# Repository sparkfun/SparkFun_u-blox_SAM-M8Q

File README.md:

SparkFun u-Blox SAM-M8Q
========================================

[*SparkFun u-Blox SAM-M8Q (GPS-15210)*](https://www.sparkfun.com/products/15210)

The SAM-M8Q is a high quality GPS with equally impressive configurability.  We broke out the basic pins and added all the supporting circuitry to make this module even easier to use.  Additionally we've mounted the M8Q on a large ground plane to maximize reception quality.

Repository Contents
-------------------

* **/Documentation** - Data sheets, additional product information
* **/Hardware** - Eagle design files (.brd, .sch)
* **/Production** - Production panel files (.brd)

Documentation
--------------
* **[Installing an Arduino Library Guide](https://learn.sparkfun.com/tutorials/installing-an-arduino-library)** - Basic information on how to install an Arduino library.
* **[Library](https://github.com/sparkfun/SparkFun_u-blox_GNSS_Arduino_Library)** - Arduino Library used with the SparkFun SAM-M8Q 
* **[Hookup Guide](https://learn.sparkfun.com/tutorials/sparkfun-gps-breakout-zoe-m8q-and-sam-m8q-hookup-guide)** - Basic hookup guide for the SparkFun SAM-M8Q.

License Information
-------------------

This product is _**open source**_! 

Please review the LICENSE.md file for license information. 

If you have any questions or concerns on licensing, please contact technical support on our [SparkFun forums](https://forum.sparkfun.com/viewforum.php?f=152).

Distributed as-is; no warranty is given.

- Your friends at SparkFun.

_<COLLABORATION CREDIT>_

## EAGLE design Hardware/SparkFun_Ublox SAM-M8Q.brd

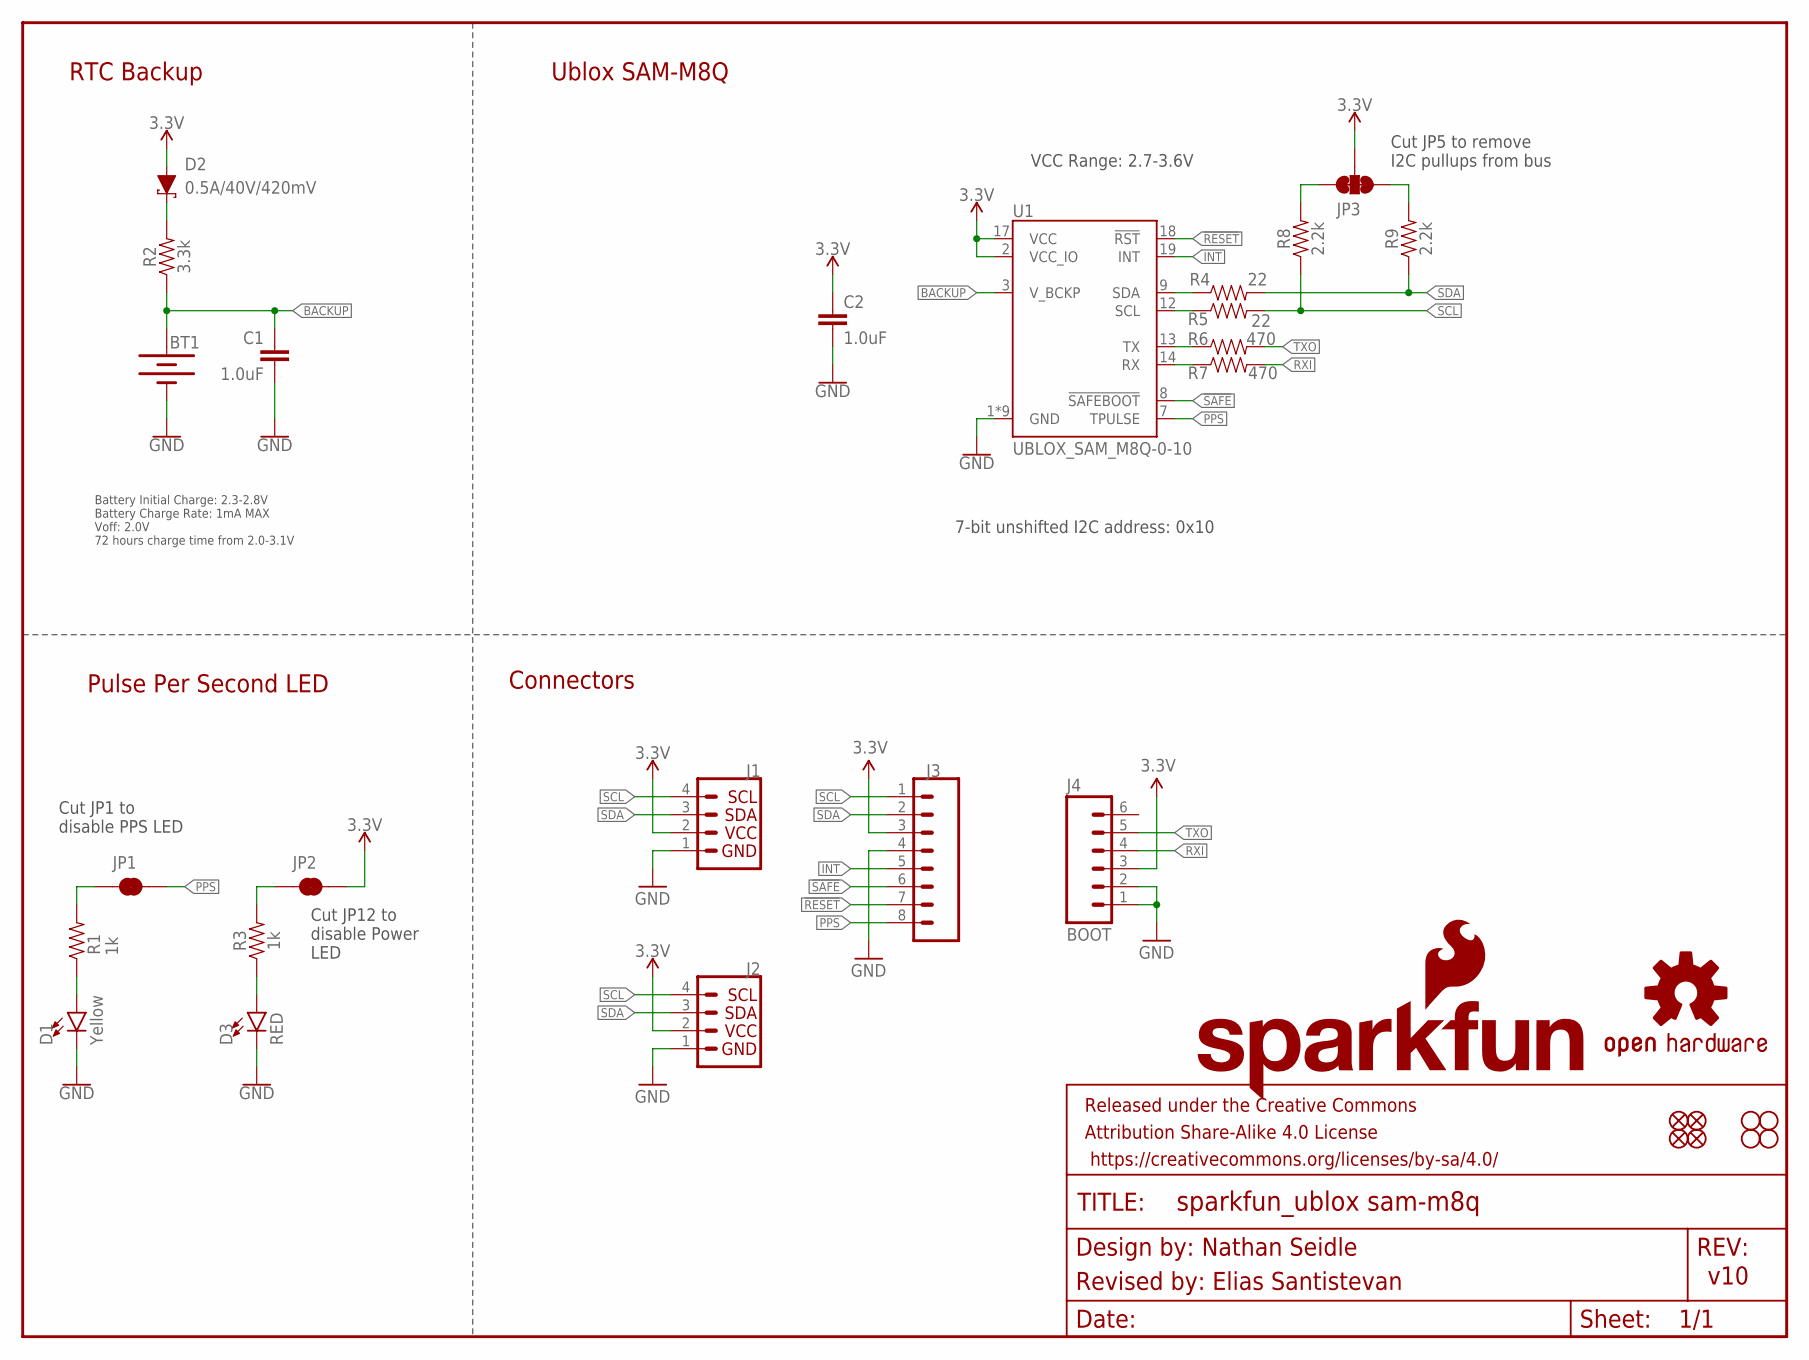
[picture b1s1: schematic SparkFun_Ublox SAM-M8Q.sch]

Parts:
BT1: 6.8MM_COIN_CELL; ML414H_IV01E
C1, C2: 1.0uF; 0603
D1: Yellow; LED-0603
D2: 0.5A/40V/420mV; SOD-323
D3: RED; LED-0603
FD1, FD2, FD3, FD4: FIDUCIALUFIDUCIAL; FIDUCIAL-MICRO
FRAME1: FRAME-LETTER; CREATIVE_COMMONS
H1, H2, H3, H4: STAND-OFF
J1, J2: Qwiic Right Angle; JST04_1MM_RA
J3: CONN_08NO_SILK_FEMALE_PTH; 1X08_NO_SILK
J4: BOOT; 1X06_NO_SILK
JP1, JP2: JUMPER-SMT_2_NC_TRACE_SILK; SMT-JUMPER_2_NC_TRACE_SILK
JP3: JUMPER-SMT_3_2-NC_TRACE_SILK; SMT-JUMPER_3_2-NC_TRACE_SILK
LOGO1: SFE_LOGO_NAME_FLAME.2_INCH; SFE_LOGO_NAME_FLAME_.2
LOGO2: OSHW-LOGOM; OSHW-LOGO-M
R1, R3: 1k; 0603
R2: 3.3k; 0603
R4, R5: 22; 0603
R6, R7: 470; 0603
R8, R9: 2.2k; 0603
U1: UBLOX_SAM_M8Q-0-10; SAM-M8Q

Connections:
3.3V: C2.1, D2.A, J1.2, J2.2, J3.3, J4.3, JP2.2, JP3.2, U1.2 (VCC_IO), U1.17 (VCC)
!RESET: J3.7, U1.18 (!RST)
!SAFE: J3.6, U1.8 (!SAFEBOOT)
BACKUP: BT1.+, C1.1, R2.1, U1.3 (V_BCKP)
GND: BT1.-, C1.2, C2.2, D1.C, D3.C, J1.1, J2.1, J3.4, J4.1, J4.2, U1.1 (GND), U1.4 (GND), U1.5 (GND), U1.6 (GND), U1.10 (GND), U1.11 (GND), U1.15 (GND), U1.16 (GND), U1.20 (GND)
INT: J3.5, U1.19 (INT)
unnamed: JP2.1, R3.2
unnamed: D1.A, R1.1
unnamed: D3.A, R3.1
unnamed: JP1.1, R1.2
unnamed: JP3.1, R9.2
unnamed: D2.C, R2.2
unnamed: JP3.3, R8.2
PPS: J3.8, JP1.2, U1.7 (TPULSE)
RXI: J4.4, R7.2
RXLV: R7.1, U1.14 (RX)
SCL: J1.4, J2.4, J3.1, R5.2, R8.1
SCL_LV: R5.1, U1.12 (SCL)
SDA: J1.3, J2.3, J3.2, R4.2, R9.1
SDA_LV: R4.1, U1.9 (SDA)
TXLV: R6.1, U1.13 (TX)
TXO: J4.5, R6.2

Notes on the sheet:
v10
7-bit unshifted I2C address: 0x10
Ublox SAM-M8Q
RTC Backup
Pulse Per Second LED
Cut JP5 to remove I2C pullups from bus
Cut JP1 to disable PPS LED
Revised by: Elias Santistevan
Nathan Seidle
Connectors
Cut JP12 to disable Power LED
VCC Range: 2.7-3.6V
Battery Initial Charge: 2.3-2.8V Battery Charge Rate: 1mA MAX Voff: 2.0V 72 hours charge time from 2.0-3.1V

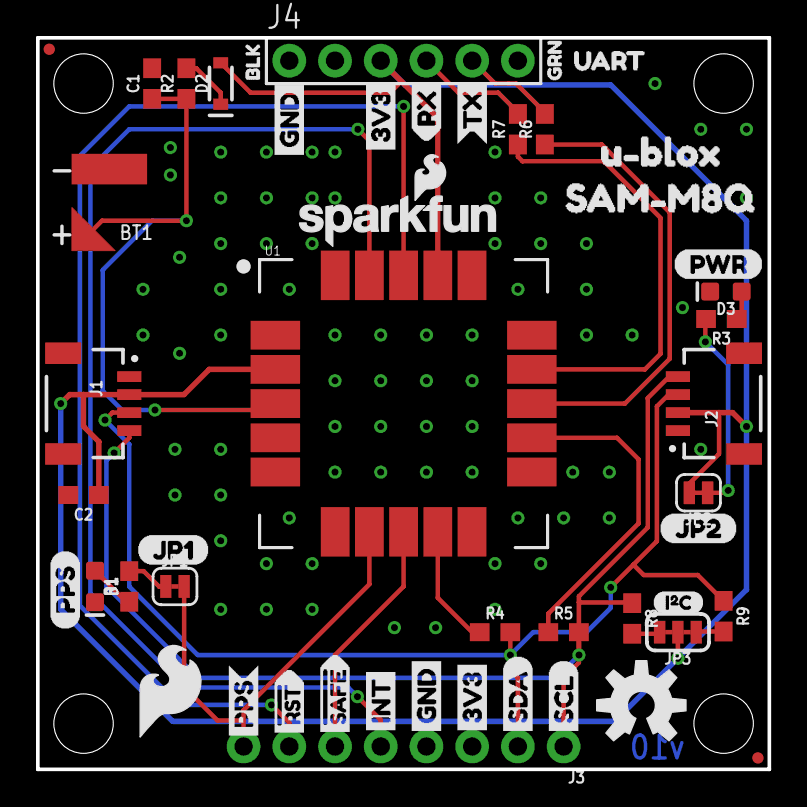
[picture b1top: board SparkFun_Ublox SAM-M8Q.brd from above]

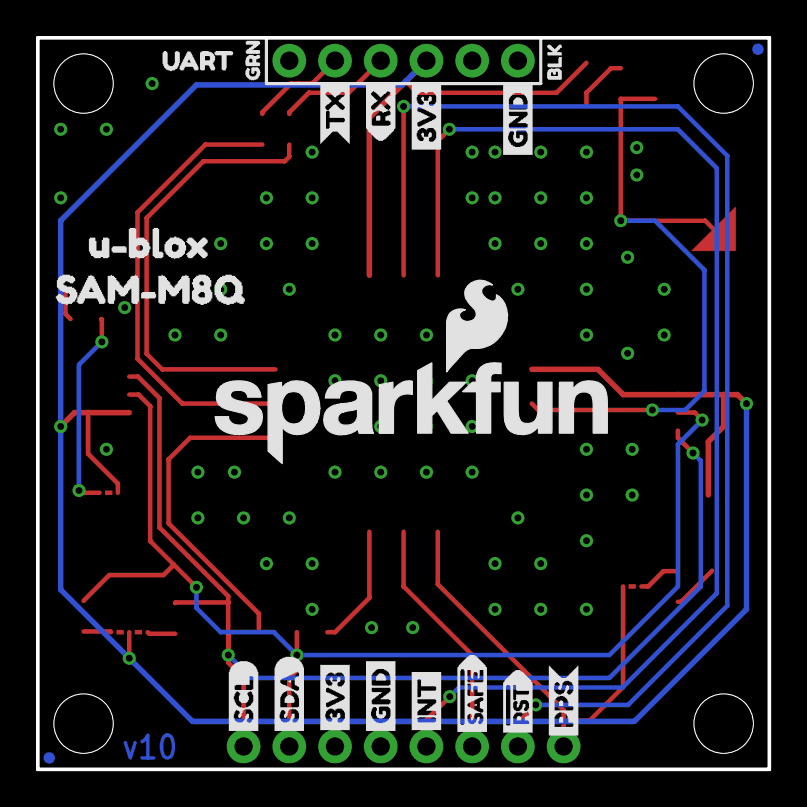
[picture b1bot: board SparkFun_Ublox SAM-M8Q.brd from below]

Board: 2 copper layers, 40.6 x 40.6 mm, 75 parts (20 on the bottom side), 22 nets.

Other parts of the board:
U$1, U$4: SDA-[)
U$2: SFE_LOGO_FLAME_.2
U$3, U$5: SCL-[)
U$6, U$7, U$27, U$32: 3V3-04
U$8, U$9, U$33, U$34: GND-04
U$10: I_SUPER2_C-()-03
U$11, U$45: UART0
U$12, U$13: BLK1
U$14, U$17: GRN2
U$15, U$16: INT8
U$18: JP10
U$19, U$20: RX6
U$21, U$25: SAM#M8Q4
U$22, U$26: U#BLOX3
U$23, U$24: TX7
U$28: SFE_LOGO_NAME_FLAME_.1
U$29: PPS0
U$30: PWR0
U$31: JP20
U$35, U$36: #RST3
U$39, U$40: #SAFE1
U$43, U$44: PPS5

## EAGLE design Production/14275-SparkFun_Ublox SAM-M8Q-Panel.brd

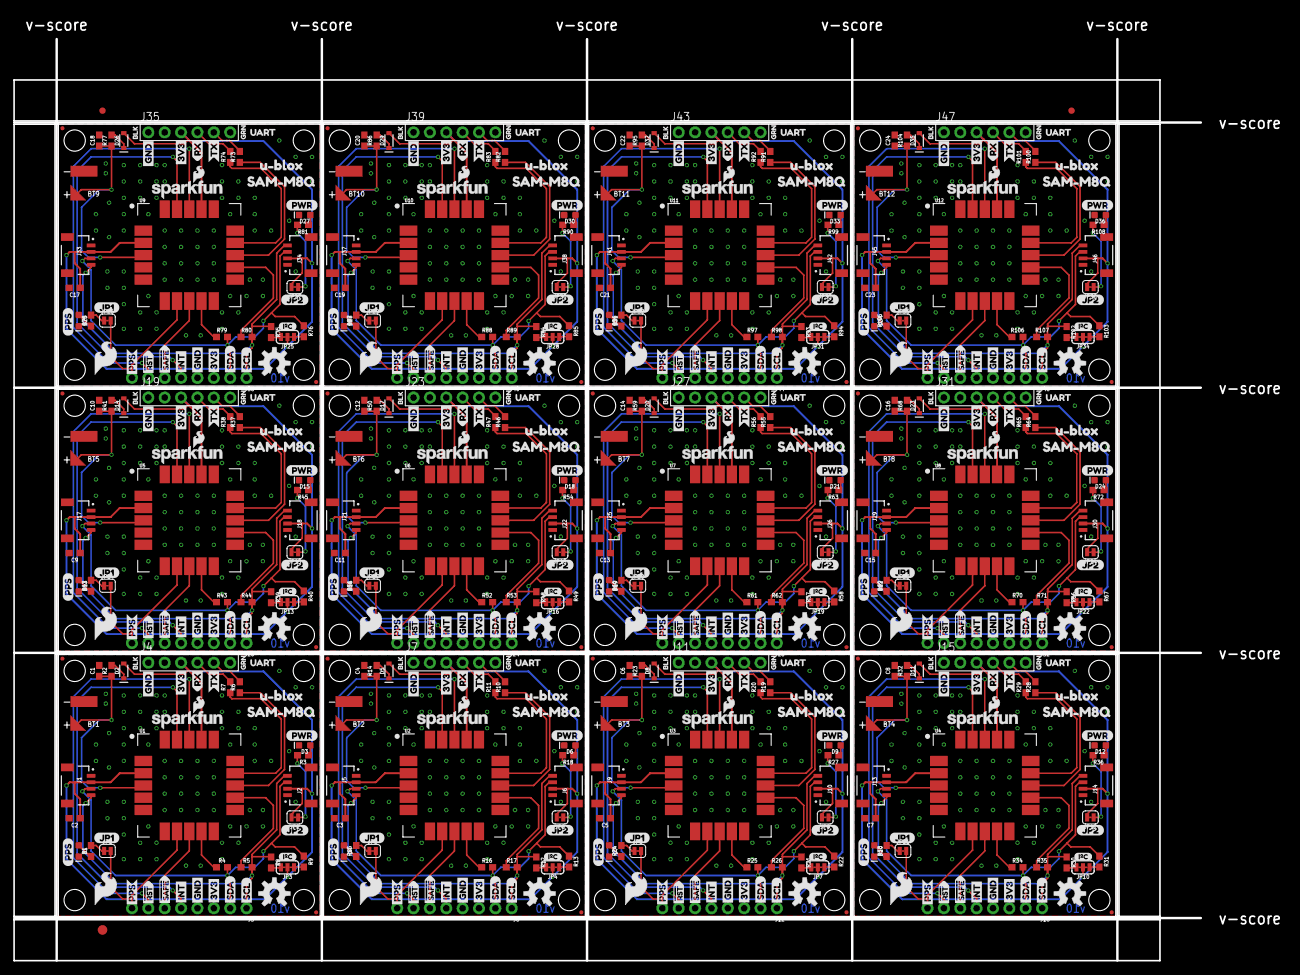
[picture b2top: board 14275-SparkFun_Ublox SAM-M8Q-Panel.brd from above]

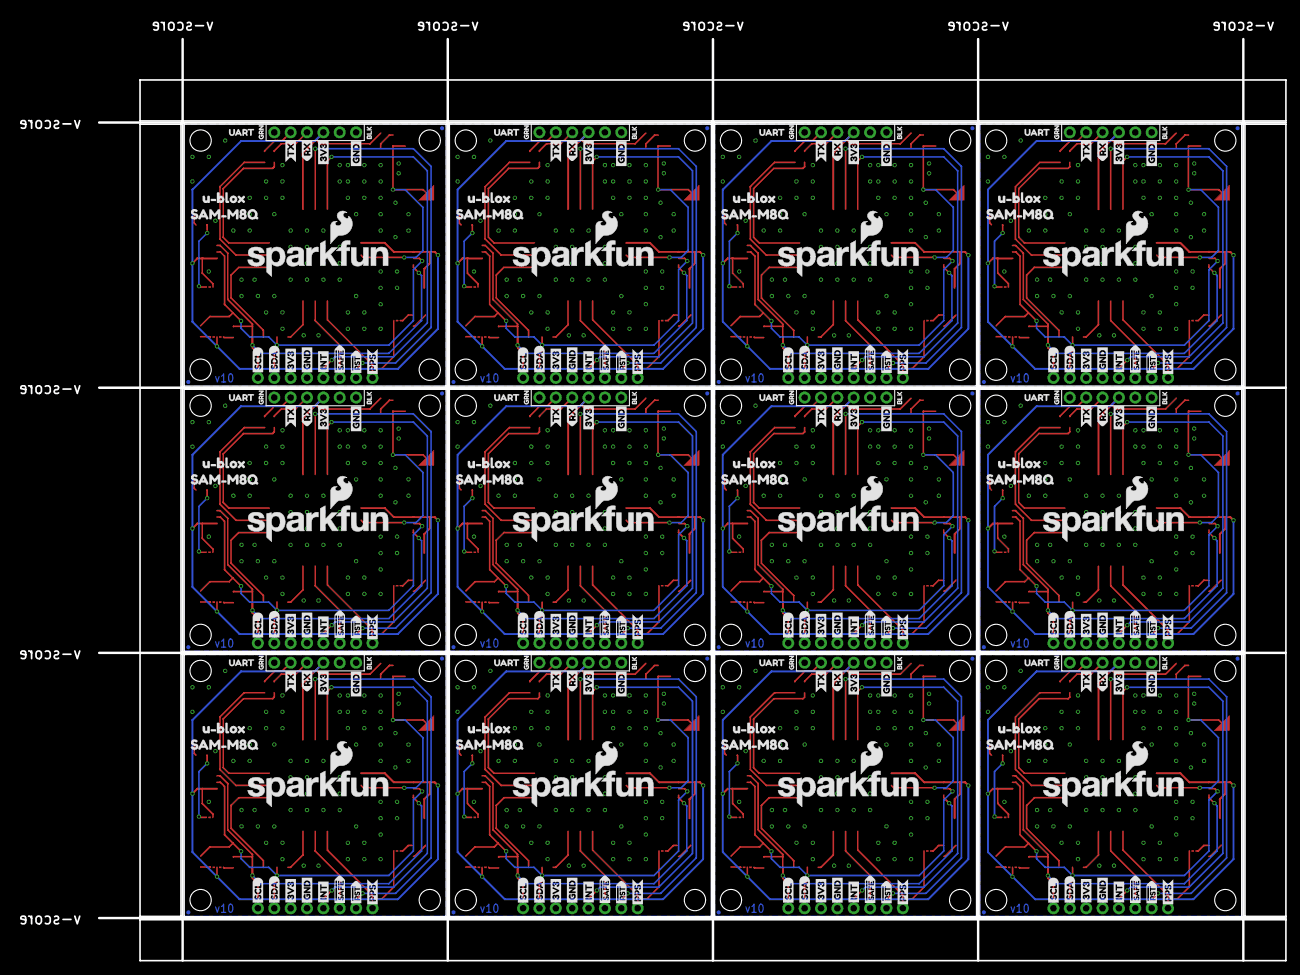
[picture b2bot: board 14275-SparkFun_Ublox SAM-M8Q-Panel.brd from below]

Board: 2 copper layers, 184.2 x 143.0 mm, 891 parts (240 on the bottom side), 264 nets.

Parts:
BT1, BT2, BT3, BT4, BT5, BT6, BT7, BT8, BT9, BT10, BT11, BT12: 6.8MM_COIN_CELL; ML414H_IV01E
C1, C2, C3, C4, C5, C6, C7, C8, C9, C10, C11, C12, C13, C14, C15, C16, C17, C18, C19, C20, C21, C22, C23, C24: 1.0uF; 0603
D1, D4, D7, D10, D13, D16, D19, D22, D25, D28, D31, D34: Yellow; LED-0603
D2, D5, D8, D11, D14, D17, D20, D23, D26, D29, D32, D35: 0.5A/40V/420mV; SOD-323
D3, D6, D9, D12, D15, D18, D21, D24, D27, D30, D33, D36: RED; LED-0603
E$1, E$2: FIDUCIAL-1X2
E$3: FIDUCIAL-1.5X3
FD1, FD2, FD3, FD4, FD5, FD6, FD7, FD8, FD9, FD10, FD11, FD12, FD13, FD14, FD15, FD16, FD17, FD18, FD19, FD20, FD21, FD22, FD23, FD24, FD25, FD26, FD27, FD28, FD29, FD30, FD31, FD32, FD33, FD34, FD35, FD36, FD37, FD38, FD39, FD40, FD41, FD42, FD43, FD44, FD45, FD46, FD47, FD48: FIDUCIALUFIDUCIAL; FIDUCIAL-MICRO
H1, H2, H3, H4, H5, H6, H7, H8, H9, H10, H11, H12, H13, H14, H15, H16, H17, H18, H19, H20, H21, H22, H23, H24, H25, H26, H27, H28, H29, H30, H31, H32, H33, H34, H35, H36, H37, H38, H39, H40, H41, H42, H43, H44, H45, H46, H47, H48: STAND-OFF
J1, J2, J5, J6, J9, J10, J13, J14, J17, J18, J21, J22, J25, J26, J29, J30, J33, J34, J37, J38, J41, J42, J45, J46: Qwiic Right Angle; JST04_1MM_RA
J3, J8, J12, J16, J20, J24, J28, J32, J36, J40, J44, J48: 1X08_NO_SILK
J4, J7, J11, J15, J19, J23, J27, J31, J35, J39, J43, J47: BOOT; 1X06_NO_SILK
JP1, JP5, JP8, JP11, JP14, JP17, JP20, JP23, JP26, JP29, JP32, JP35: SMT-JUMPER_2_NC_TRACE_SILK
JP2, JP6, JP9, JP12, JP15, JP18, JP21, JP24, JP27, JP30, JP33, JP36: JUMPER-SMT_2_NC_TRACE_SILK; SMT-JUMPER_2_NC_TRACE_SILK
JP3, JP4, JP7, JP10, JP13, JP16, JP19, JP22, JP25, JP28, JP31, JP34: JUMPER-SMT_3_2-NC_TRACE_SILK; SMT-JUMPER_3_2-NC_TRACE_SILK
LOGO1, LOGO4, LOGO6, LOGO8, LOGO10, LOGO12, LOGO14, LOGO16, LOGO18, LOGO20, LOGO22, LOGO24: SFE_LOGO_NAME_FLAME.2_INCH; SFE_LOGO_NAME_FLAME_.2
LOGO2, LOGO3, LOGO5, LOGO7, LOGO9, LOGO11, LOGO13, LOGO15, LOGO17, LOGO19, LOGO21, LOGO23: OSHW-LOGOM; OSHW-LOGO-M
R1, R3, R15, R18, R24, R27, R33, R36, R42, R45, R51, R54, R60, R63, R69, R72, R78, R81, R87, R90, R96, R99, R105, R108: 1k; 0603
R2, R14, R23, R32, R41, R50, R59, R68, R77, R86, R95, R104: 3.3k; 0603
R4, R5, R16, R17, R25, R26, R34, R35, R43, R44, R52, R53, R61, R62, R70, R71, R79, R80, R88, R89, R97, R98, R106, R107: 22; 0603
R6, R7, R10, R11, R19, R20, R28, R29, R37, R38, R46, R47, R55, R56, R64, R65, R73, R74, R82, R83, R91, R92, R100, R101: 470; 0603
R8, R9, R12, R13, R21, R22, R30, R31, R39, R40, R48, R49, R57, R58, R66, R67, R75, R76, R84, R85, R93, R94, R102, R103: 2.2k; 0603
U1, U2, U3, U4, U5, U6, U7, U8, U9, U10, U11, U12: UBLOX_SAM_M8Q-0-10; SAM-M8Q
U$1, U$4, U$37, U$41, U$83, U$85, U$124, U$126, U$165, U$167, U$206, U$208, U$247, U$249, U$288, U$290, U$329, U$331, U$370, U$372, U$411, U$413, U$452, U$454: SDA-[)
U$2, U$80, U$121, U$162, U$203, U$244, U$285, U$326, U$367, U$408, U$449, U$490: SFE_LOGO_FLAME_.2
U$3, U$5, U$38, U$42, U$84, U$86, U$125, U$127, U$166, U$168, U$207, U$209, U$248, U$250, U$289, U$291, U$330, U$332, U$371, U$373, U$412, U$414, U$453, U$455: SCL-[)
U$6, U$7, U$27, U$32, U$46, U$47, U$62, U$63, U$87, U$88, U$103, U$104, U$128, U$129, U$144, U$145, U$169, U$170, U$185, U$186, U$210, U$211, U$226, U$227, U$251, U$252, U$267, U$268, U$292, U$293, U$308, U$309, U$333, U$334, U$349, U$350, U$374, U$375, U$390, U$391, U$415, U$416, U$431, U$432, U$456, U$457, U$472, U$473: 3V3-04
U$8, U$9, U$33, U$34, U$48, U$49, U$64, U$65, U$89, U$90, U$105, U$106, U$130, U$131, U$146, U$147, U$171, U$172, U$187, U$188, U$212, U$213, U$228, U$229, U$253, U$254, U$269, U$270, U$294, U$295, U$310, U$311, U$335, U$336, U$351, U$352, U$376, U$377, U$392, U$393, U$417, U$418, U$433, U$434, U$458, U$459, U$474, U$475: GND-04
U$10, U$50, U$91, U$132, U$173, U$214, U$255, U$296, U$337, U$378, U$419, U$460: I_SUPER2_C-()-03
U$11, U$45, U$72, U$73, U$113, U$114, U$154, U$155, U$195, U$196, U$236, U$237, U$277, U$278, U$318, U$319, U$359, U$360, U$400, U$401, U$441, U$442, U$482, U$483: UART0
U$12, U$13, U$74, U$75, U$115, U$116, U$156, U$157, U$197, U$198, U$238, U$239, U$279, U$280, U$320, U$321, U$361, U$362, U$402, U$403, U$443, U$444, U$484, U$485: BLK1
U$14, U$17, U$76, U$77, U$117, U$118, U$158, U$159, U$199, U$200, U$240, U$241, U$281, U$282, U$322, U$323, U$363, U$364, U$404, U$405, U$445, U$446, U$486, U$487: GRN2
U$15, U$16, U$51, U$52, U$92, U$93, U$133, U$134, U$174, U$175, U$215, U$216, U$256, U$257, U$297, U$298, U$338, U$339, U$379, U$380, U$420, U$421, U$461, U$462: INT8
U$18, U$78, U$119, U$160, U$201, U$242, U$283, U$324, U$365, U$406, U$447, U$488: JP10
U$19, U$20, U$53, U$54, U$94, U$95, U$135, U$136, U$176, U$177, U$217, U$218, U$258, U$259, U$299, U$300, U$340, U$341, U$381, U$382, U$422, U$423, U$463, U$464: RX6
U$21, U$25, U$55, U$60, U$96, U$101, U$137, U$142, U$178, U$183, U$219, U$224, U$260, U$265, U$301, U$306, U$342, U$347, U$383, U$388, U$424, U$429, U$465, U$470: SAM#M8Q4
U$22, U$26, U$58, U$59, U$99, U$100, U$140, U$141, U$181, U$182, U$222, U$223, U$263, U$264, U$304, U$305, U$345, U$346, U$386, U$387, U$427, U$428, U$468, U$469: U#BLOX3
U$23, U$24, U$56, U$57, U$97, U$98, U$138, U$139, U$179, U$180, U$220, U$221, U$261, U$262, U$302, U$303, U$343, U$344, U$384, U$385, U$425, U$426, U$466, U$467: TX7
U$28, U$82, U$123, U$164, U$205, U$246, U$287, U$328, U$369, U$410, U$451, U$492: SFE_LOGO_NAME_FLAME_.1
U$29, U$61, U$102, U$143, U$184, U$225, U$266, U$307, U$348, U$389, U$430, U$471: PPS0
U$30, U$79, U$120, U$161, U$202, U$243, U$284, U$325, U$366, U$407, U$448, U$489: PWR0
U$31, U$81, U$122, U$163, U$204, U$245, U$286, U$327, U$368, U$409, U$450, U$491: JP20
U$35, U$36, U$66, U$67, U$107, U$108, U$148, U$149, U$189, U$190, U$230, U$231, U$271, U$272, U$312, U$313, U$353, U$354, U$394, U$395, U$435, U$436, U$476, U$477: #RST3
U$39, U$40, U$68, U$69, U$109, U$110, U$150, U$151, U$191, U$192, U$232, U$233, U$273, U$274, U$314, U$315, U$355, U$356, U$396, U$397, U$437, U$438, U$478, U$479: #SAFE1
U$43, U$44, U$70, U$71, U$111, U$112, U$152, U$153, U$193, U$194, U$234, U$235, U$275, U$276, U$316, U$317, U$357, U$358, U$398, U$399, U$439, U$440, U$480, U$481: PPS5

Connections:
3.3V: C2.1, D2.A, J1.2, J2.2, J3.3, J4.3, JP2.2, JP3.2, U1.2, U1.17
3.3V1: C3.1, D5.A, J5.2, J6.2, J7.3, J8.3, JP4.2, JP6.2, U2.2, U2.17
3.3V2: C5.1, D8.A, J9.2, J10.2, J11.3, J12.3, JP7.2, JP9.2, U3.2, U3.17
3.3V3: C7.1, D11.A, J13.2, J14.2, J15.3, J16.3, JP10.2, JP12.2, U4.2, U4.17
3.3V4: C9.1, D14.A, J17.2, J18.2, J19.3, J20.3, JP13.2, JP15.2, U5.2, U5.17
3.3V5: C11.1, D17.A, J21.2, J22.2, J23.3, J24.3, JP16.2, JP18.2, U6.2, U6.17
3.3V6: C13.1, D20.A, J25.2, J26.2, J27.3, J28.3, JP19.2, JP21.2, U7.2, U7.17
3.3V7: C15.1, D23.A, J29.2, J30.2, J31.3, J32.3, JP22.2, JP24.2, U8.2, U8.17
3.3V8: C17.1, D26.A, J33.2, J34.2, J35.3, J36.3, JP25.2, JP27.2, U9.2, U9.17
3.3V9: C19.1, D29.A, J37.2, J38.2, J39.3, J40.3, JP28.2, JP30.2, U10.2, U10.17
3.3V10: C21.1, D32.A, J41.2, J42.2, J43.3, J44.3, JP31.2, JP33.2, U11.2, U11.17
3.3V11: C23.1, D35.A, J45.2, J46.2, J47.3, J48.3, JP34.2, JP36.2, U12.2, U12.17
!RESET: J3.7, U1.18
!RESET1: J8.7, U2.18
!RESET2: J12.7, U3.18
!RESET3: J16.7, U4.18
!RESET4: J20.7, U5.18
!RESET5: J24.7, U6.18
!RESET6: J28.7, U7.18
!RESET7: J32.7, U8.18
!RESET8: J36.7, U9.18
!RESET9: J40.7, U10.18
!RESET10: J44.7, U11.18
!RESET11: J48.7, U12.18
!SAFE: J3.6, U1.8
!SAFE1: J8.6, U2.8
!SAFE2: J12.6, U3.8
!SAFE3: J16.6, U4.8
!SAFE4: J20.6, U5.8
!SAFE5: J24.6, U6.8
!SAFE6: J28.6, U7.8
!SAFE7: J32.6, U8.8
!SAFE8: J36.6, U9.8
!SAFE9: J40.6, U10.8
!SAFE10: J44.6, U11.8
!SAFE11: J48.6, U12.8
BACKUP: BT1.+, C1.1, R2.1, U1.3
BACKUP1: BT2.+, C4.1, R14.1, U2.3
BACKUP2: BT3.+, C6.1, R23.1, U3.3
BACKUP3: BT4.+, C8.1, R32.1, U4.3
BACKUP4: BT5.+, C10.1, R41.1, U5.3
BACKUP5: BT6.+, C12.1, R50.1, U6.3
BACKUP6: BT7.+, C14.1, R59.1, U7.3
BACKUP7: BT8.+, C16.1, R68.1, U8.3
BACKUP8: BT9.+, C18.1, R77.1, U9.3
BACKUP9: BT10.+, C20.1, R86.1, U10.3
BACKUP10: BT11.+, C22.1, R95.1, U11.3
BACKUP11: BT12.+, C24.1, R104.1, U12.3
GND: BT1.-, C1.2, C2.2, D1.C, D3.C, J1.1, J2.1, J3.4, J4.1, J4.2, U1.1, U1.4, U1.5, U1.6, U1.10, U1.11, U1.15, U1.16, U1.20
GND1: BT2.-, C3.2, C4.2, D4.C, D6.C, J5.1, J6.1, J7.1, J7.2, J8.4, U2.1, U2.4, U2.5, U2.6, U2.10, U2.11, U2.15, U2.16, U2.20
GND2: BT3.-, C5.2, C6.2, D7.C, D9.C, J9.1, J10.1, J11.1, J11.2, J12.4, U3.1, U3.4, U3.5, U3.6, U3.10, U3.11, U3.15, U3.16, U3.20
GND3: BT4.-, C7.2, C8.2, D10.C, D12.C, J13.1, J14.1, J15.1, J15.2, J16.4, U4.1, U4.4, U4.5, U4.6, U4.10, U4.11, U4.15, U4.16, U4.20
GND4: BT5.-, C9.2, C10.2, D13.C, D15.C, J17.1, J18.1, J19.1, J19.2, J20.4, U5.1, U5.4, U5.5, U5.6, U5.10, U5.11, U5.15, U5.16, U5.20
GND5: BT6.-, C11.2, C12.2, D16.C, D18.C, J21.1, J22.1, J23.1, J23.2, J24.4, U6.1, U6.4, U6.5, U6.6, U6.10, U6.11, U6.15, U6.16, U6.20
GND6: BT7.-, C13.2, C14.2, D19.C, D21.C, J25.1, J26.1, J27.1, J27.2, J28.4, U7.1, U7.4, U7.5, U7.6, U7.10, U7.11, U7.15, U7.16, U7.20
GND7: BT8.-, C15.2, C16.2, D22.C, D24.C, J29.1, J30.1, J31.1, J31.2, J32.4, U8.1, U8.4, U8.5, U8.6, U8.10, U8.11, U8.15, U8.16, U8.20
GND8: BT9.-, C17.2, C18.2, D25.C, D27.C, J33.1, J34.1, J35.1, J35.2, J36.4, U9.1, U9.4, U9.5, U9.6, U9.10, U9.11, U9.15, U9.16, U9.20
GND9: BT10.-, C19.2, C20.2, D28.C, D30.C, J37.1, J38.1, J39.1, J39.2, J40.4, U10.1, U10.4, U10.5, U10.6, U10.10, U10.11, U10.15, U10.16, U10.20
GND10: BT11.-, C21.2, C22.2, D31.C, D33.C, J41.1, J42.1, J43.1, J43.2, J44.4, U11.1, U11.4, U11.5, U11.6, U11.10, U11.11, U11.15, U11.16, U11.20
GND11: BT12.-, C23.2, C24.2, D34.C, D36.C, J45.1, J46.1, J47.1, J47.2, J48.4, U12.1, U12.4, U12.5, U12.6, U12.10, U12.11, U12.15, U12.16, U12.20
INT: J3.5, U1.19
INT1: J8.5, U2.19
INT2: J12.5, U3.19
INT3: J16.5, U4.19
INT4: J20.5, U5.19
INT5: J24.5, U6.19
INT6: J28.5, U7.19
INT7: J32.5, U8.19
INT8: J36.5, U9.19
INT9: J40.5, U10.19
INT10: J44.5, U11.19
INT11: J48.5, U12.19
unnamed: JP2.1, R3.2
unnamed: D1.A, R1.1
unnamed: D3.A, R3.1
unnamed: JP1.1, R1.2
unnamed: JP3.1, R9.2
unnamed: D2.C, R2.2
unnamed: JP4.1, R13.2
unnamed: JP3.3, R8.2
unnamed: JP4.3, R12.2
unnamed: D4.A, R15.1
unnamed: JP5.1, R15.2
unnamed: D5.C, R14.2
unnamed: JP6.1, R18.2
unnamed: D6.A, R18.1
unnamed: JP7.1, R22.2
unnamed: JP7.3, R21.2
unnamed: D7.A, R24.1
unnamed: JP8.1, R24.2
unnamed: D8.C, R23.2
unnamed: JP9.1, R27.2
unnamed: D9.A, R27.1
unnamed: JP10.1, R31.2
unnamed: JP10.3, R30.2
unnamed: D10.A, R33.1
unnamed: JP11.1, R33.2
unnamed: D11.C, R32.2
unnamed: JP12.1, R36.2
unnamed: D12.A, R36.1
unnamed: JP13.1, R40.2
unnamed: JP13.3, R39.2
unnamed: D13.A, R42.1
unnamed: JP14.1, R42.2
unnamed: D14.C, R41.2
unnamed: JP15.1, R45.2
unnamed: D15.A, R45.1
unnamed: JP16.1, R49.2
unnamed: JP16.3, R48.2
unnamed: D16.A, R51.1
unnamed: JP17.1, R51.2
unnamed: D17.C, R50.2
unnamed: JP18.1, R54.2
unnamed: D18.A, R54.1
unnamed: JP19.1, R58.2
unnamed: JP19.3, R57.2
unnamed: D19.A, R60.1
unnamed: JP20.1, R60.2
unnamed: D20.C, R59.2
unnamed: JP21.1, R63.2
unnamed: D21.A, R63.1
unnamed: JP22.1, R67.2
unnamed: JP22.3, R66.2
unnamed: D22.A, R69.1
unnamed: JP23.1, R69.2
unnamed: D23.C, R68.2
unnamed: JP24.1, R72.2
unnamed: D24.A, R72.1
unnamed: JP25.1, R76.2
unnamed: JP25.3, R75.2
unnamed: D25.A, R78.1
unnamed: JP26.1, R78.2
unnamed: D26.C, R77.2
unnamed: JP27.1, R81.2
unnamed: D27.A, R81.1
unnamed: JP28.1, R85.2
unnamed: JP28.3, R84.2
unnamed: D28.A, R87.1
unnamed: JP29.1, R87.2
unnamed: D29.C, R86.2
unnamed: JP30.1, R90.2
unnamed: D30.A, R90.1
unnamed: JP31.1, R94.2
unnamed: JP31.3, R93.2
unnamed: D31.A, R96.1
unnamed: JP32.1, R96.2
unnamed: D32.C, R95.2
unnamed: JP33.1, R99.2
unnamed: D33.A, R99.1
unnamed: JP34.1, R103.2
unnamed: JP34.3, R102.2
unnamed: D34.A, R105.1
unnamed: JP35.1, R105.2
unnamed: D35.C, R104.2
unnamed: JP36.1, R108.2
unnamed: D36.A, R108.1
PPS: J3.8, JP1.2, U1.7
PPS1: J8.8, JP5.2, U2.7
PPS2: J12.8, JP8.2, U3.7
PPS3: J16.8, JP11.2, U4.7
PPS4: J20.8, JP14.2, U5.7
PPS5: J24.8, JP17.2, U6.7
PPS6: J28.8, JP20.2, U7.7
PPS7: J32.8, JP23.2, U8.7
PPS8: J36.8, JP26.2, U9.7
PPS9: J40.8, JP29.2, U10.7
PPS10: J44.8, JP32.2, U11.7
PPS11: J48.8, JP35.2, U12.7
RXI: J4.4, R7.2
RXI1: J7.4, R11.2
RXI2: J11.4, R20.2
RXI3: J15.4, R29.2
RXI4: J19.4, R38.2
RXI5: J23.4, R47.2
RXI6: J27.4, R56.2
RXI7: J31.4, R65.2
RXI8: J35.4, R74.2
RXI9: J39.4, R83.2
RXI10: J43.4, R92.2
RXI11: J47.4, R101.2
RXLV: R7.1, U1.14
RXLV1: R11.1, U2.14
RXLV2: R20.1, U3.14
RXLV3: R29.1, U4.14
RXLV4: R38.1, U5.14
RXLV5: R47.1, U6.14
RXLV6: R56.1, U7.14
RXLV7: R65.1, U8.14
RXLV8: R74.1, U9.14
RXLV9: R83.1, U10.14
RXLV10: R92.1, U11.14
RXLV11: R101.1, U12.14
SCL: J1.4, J2.4, J3.1, R5.2, R8.1
SCL1: J5.4, J6.4, J8.1, R12.1, R17.2
SCL2: J9.4, J10.4, J12.1, R21.1, R26.2
SCL3: J13.4, J14.4, J16.1, R30.1, R35.2
SCL4: J17.4, J18.4, J20.1, R39.1, R44.2
SCL5: J21.4, J22.4, J24.1, R48.1, R53.2
SCL6: J25.4, J26.4, J28.1, R57.1, R62.2
SCL7: J29.4, J30.4, J32.1, R66.1, R71.2
SCL8: J33.4, J34.4, J36.1, R75.1, R80.2
SCL9: J37.4, J38.4, J40.1, R84.1, R89.2
SCL10: J41.4, J42.4, J44.1, R93.1, R98.2
SCL11: J45.4, J46.4, J48.1, R102.1, R107.2
SCL_LV: R5.1, U1.12
SCL_LV1: R17.1, U2.12
SCL_LV2: R26.1, U3.12
SCL_LV3: R35.1, U4.12
SCL_LV4: R44.1, U5.12
SCL_LV5: R53.1, U6.12
SCL_LV6: R62.1, U7.12
SCL_LV7: R71.1, U8.12
SCL_LV8: R80.1, U9.12
SCL_LV9: R89.1, U10.12
SCL_LV10: R98.1, U11.12
SCL_LV11: R107.1, U12.12
SDA: J1.3, J2.3, J3.2, R4.2, R9.1
SDA1: J5.3, J6.3, J8.2, R13.1, R16.2
SDA2: J9.3, J10.3, J12.2, R22.1, R25.2
SDA3: J13.3, J14.3, J16.2, R31.1, R34.2
SDA4: J17.3, J18.3, J20.2, R40.1, R43.2
SDA5: J21.3, J22.3, J24.2, R49.1, R52.2
SDA6: J25.3, J26.3, J28.2, R58.1, R61.2
SDA7: J29.3, J30.3, J32.2, R67.1, R70.2
SDA8: J33.3, J34.3, J36.2, R76.1, R79.2
SDA9: J37.3, J38.3, J40.2, R85.1, R88.2
SDA10: J41.3, J42.3, J44.2, R94.1, R97.2
SDA11: J45.3, J46.3, J48.2, R103.1, R106.2
SDA_LV: R4.1, U1.9
SDA_LV1: R16.1, U2.9
SDA_LV2: R25.1, U3.9
SDA_LV3: R34.1, U4.9
SDA_LV4: R43.1, U5.9
SDA_LV5: R52.1, U6.9
SDA_LV6: R61.1, U7.9
SDA_LV7: R70.1, U8.9
SDA_LV8: R79.1, U9.9
SDA_LV9: R88.1, U10.9
SDA_LV10: R97.1, U11.9
SDA_LV11: R106.1, U12.9
TXLV: R6.1, U1.13
TXLV1: R10.1, U2.13
TXLV2: R19.1, U3.13
TXLV3: R28.1, U4.13
TXLV4: R37.1, U5.13
TXLV5: R46.1, U6.13
TXLV6: R55.1, U7.13
TXLV7: R64.1, U8.13
TXLV8: R73.1, U9.13
TXLV9: R82.1, U10.13
TXLV10: R91.1, U11.13
TXLV11: R100.1, U12.13
TXO: J4.5, R6.2
TXO1: J7.5, R10.2
TXO2: J11.5, R19.2
TXO3: J15.5, R28.2
TXO4: J19.5, R37.2
TXO5: J23.5, R46.2
TXO6: J27.5, R55.2
TXO7: J31.5, R64.2
TXO8: J35.5, R73.2
TXO9: J39.5, R82.2
TXO10: J43.5, R91.2
TXO11: J47.5, R100.2

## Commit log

2019-02-06 Initial Commit (see description)
    * Copies from SparkX repo
    * Changed all trace widths to 10 mil, VCC to 12 mil
    * Adds reflowable battery
    * Adjusts Schematic organization
    * Adds "Design By" and "Revised By"
    * Adds SparkFun silk
2019-02-06 Replaces all part with SparkFun parts, moves temp libarary parts to SparkFun Eagle libararies
2019-02-06 Changes all drill sizes to 15 mil, adjust schematic labels
2019-02-07 Updates GPS module with updated part, adds VCC range and Battery text to schematic
2019-02-11 Changes JP12 to JP2, fixes SDA trace, adds silk on top
2019-02-12 Changes polygon width to 10 mil and dimension to 8 mil
2019-02-13 Adds measurments to measures layer, fixes power LED air wire, adjusts bottom dimension line
2019-02-14 Created panel v10
2019-03-01 Updates Readme
2019-03-27 Updates address to correct default and only: 0x42

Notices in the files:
parts and their libraries:
SparkFun-Resistors: Licensing: Creative Commons ShareAlike 4.0 International - https://creativecommons.org/licenses/by-sa/4.0
SparkFun-Aesthetics: Released under the Creative Commons Attribution Share-Alike 4.0 License
SparkFun-Aesthetics: https://creativecommons.org/licenses/by-sa/4.0
